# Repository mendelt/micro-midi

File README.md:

# micro-midi

This is a KiCad pcb design for a Midi input and output breakout board for microcontroller projects.

## Datasheets
- [6n137](https://www.vishay.com/docs/84732/6n137.pdf)

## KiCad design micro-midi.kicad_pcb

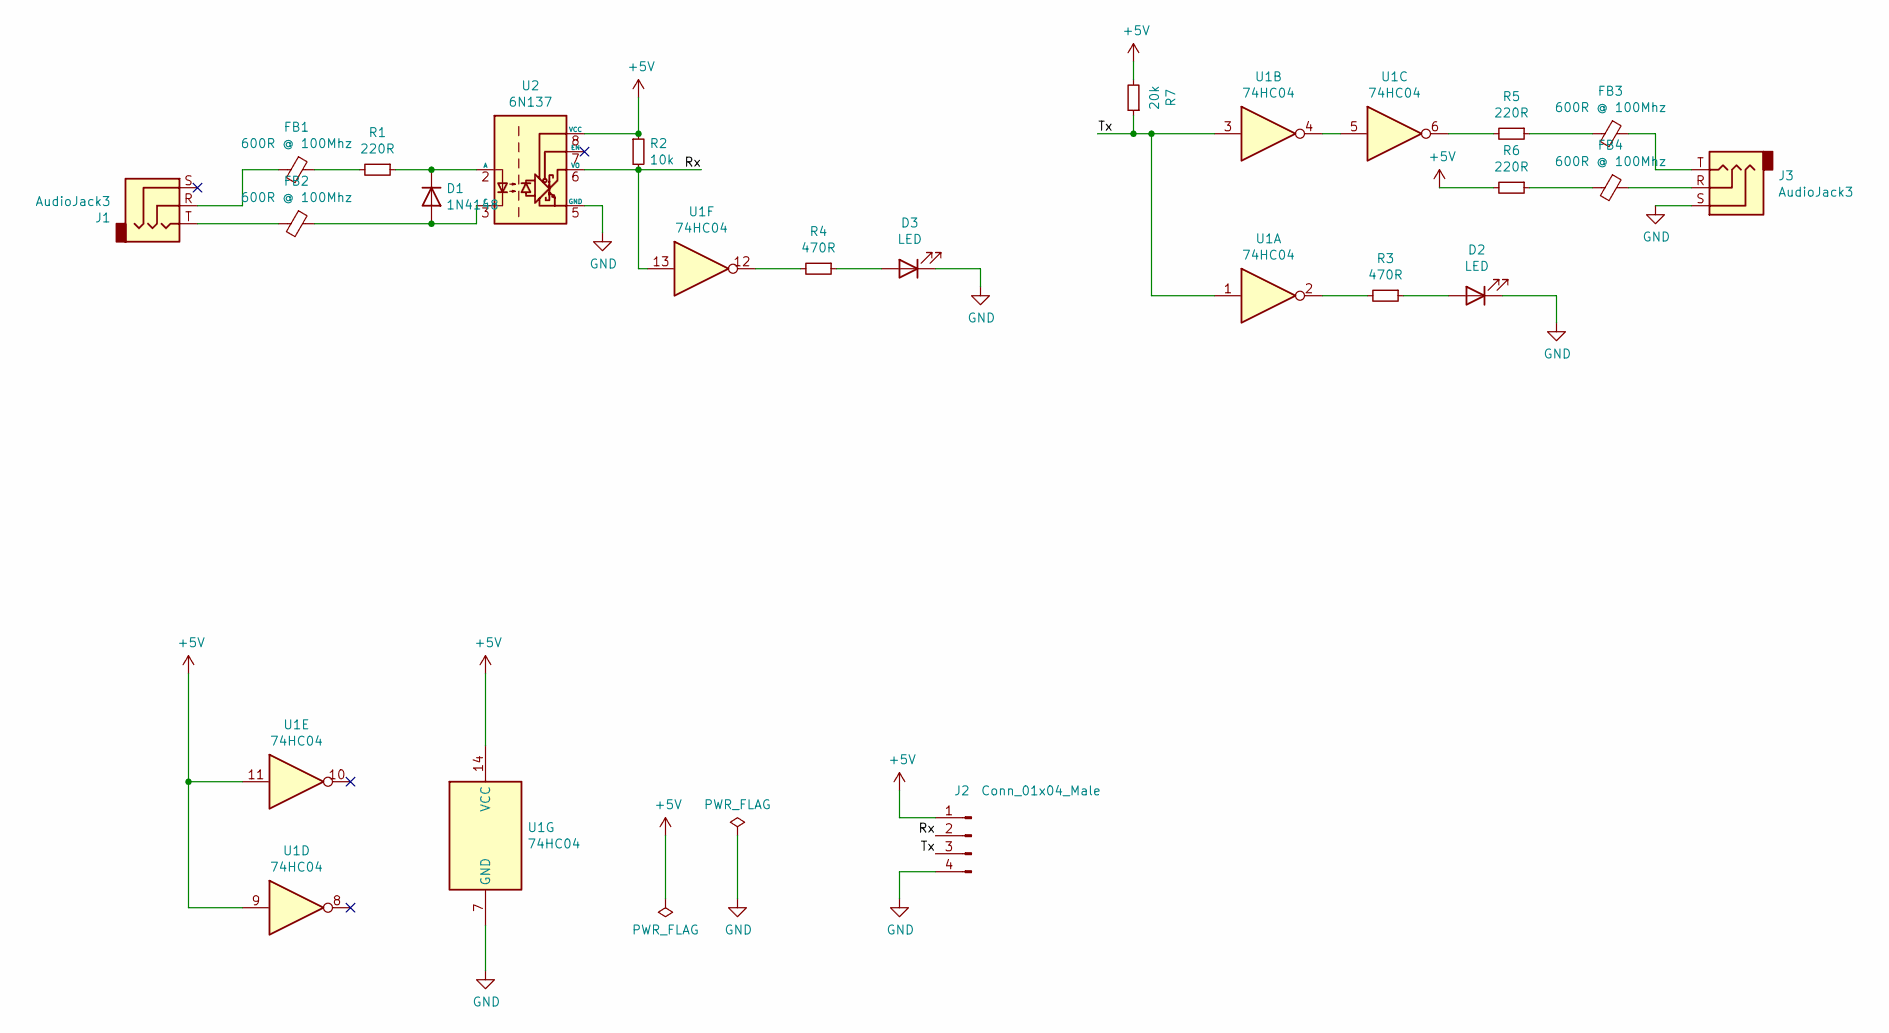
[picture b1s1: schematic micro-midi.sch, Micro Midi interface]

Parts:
D1: 1N4148; D_0805_2012Metric_Pad1.15x1.40mm_HandSolder
D2, D3: LED; LED_0805_2012Metric_Pad1.15x1.40mm_HandSolder
FB1, FB2, FB3, FB4: 600R @ 100Mhz; R_0805_2012Metric_Pad1.15x1.40mm_HandSolder; Mouser 81-BLM21A601F
J1, J3: AudioJack3; Jack_3.5mm_QingPu_WQP-PJ398SM_Vertical_CircularHoles
J2: Conn_01x04_Male; PinHeader_1x04_P2.54mm_Vertical
R1, R5, R6: 220R; R_0805_2012Metric_Pad1.15x1.40mm_HandSolder; Mouser 667-ERJ-6ENF2200V
R2: 10k; R_0805_2012Metric_Pad1.15x1.40mm_HandSolder; Mouser 667-ERJ-6ENF1002V
R3, R4: 470R; R_0805_2012Metric_Pad1.15x1.40mm_HandSolder; Mouser 667-ERJ-6ENF4700V
R7: 20k; R_0805_2012Metric_Pad1.15x1.40mm_HandSolder; Mouser 667-ERJ-6ENF2002V
U1: 74HC04; SOIC-14_3.9x8.7mm_P1.27mm
U2: 6N137; PowerIntegrations_SMD-8

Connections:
+5V: J2.1, R2.1, R6.2, R7.2, U1.9, U1.11, U1.14 (VCC), U2.8 (VCC)
/Rx: J2.2, R2.2, U1.13, U2.6 (VO)
/Tx: J2.3, R7.1, U1.1, U1.3
GND: D2.1 (K), D3.1 (K), J2.4, J3.S, U1.7 (GND), U2.5 (GND)
unnamed: D1.1 (K), R1.1, U2.2 (A)
unnamed: D1.2 (A), FB2.1, U2.3 (C)
unnamed: D2.2 (A), R3.1
unnamed: D3.2 (A), R4.1
unnamed: FB1.1, R1.2
unnamed: FB1.2, J1.R
unnamed: FB2.2, J1.T
unnamed: FB3.1, J3.T
unnamed: FB3.2, R5.1
unnamed: FB4.1, J3.R
unnamed: FB4.2, R6.1
unnamed: R3.2, U1.2
unnamed: R4.2, U1.12
unnamed: R5.2, U1.6
unnamed: U1.4, U1.5

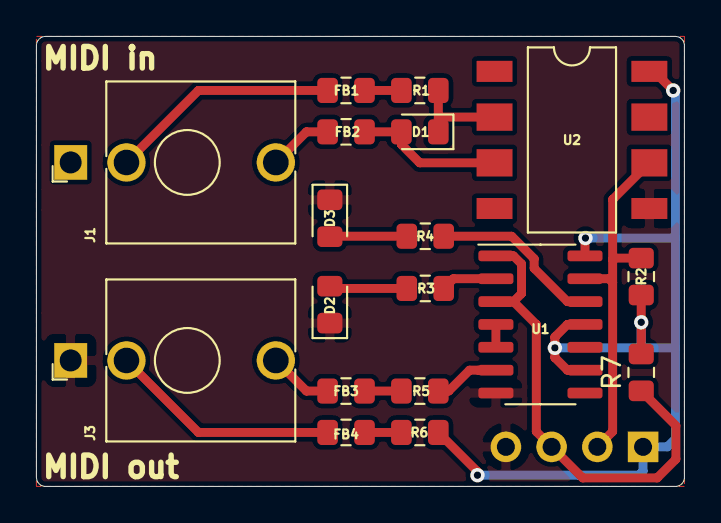
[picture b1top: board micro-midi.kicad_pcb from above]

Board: 2 copper layers, 36.0 x 25.0 mm, 19 parts (1 on the bottom side), 19 nets.

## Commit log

2020-03-26 Initialize project with first schema
2020-03-27 add footprints first try and create ratsnest
2020-03-29 add midi-out and activity leds
2020-04-16 add power flags to fix errors
2020-04-16 remove midi thru
2020-04-16 fix midi out led and ground
2020-04-16 fix midi out and add termination resistors
2020-04-21 set up schematic page settings
2020-04-28 found the right footprint for the 6n137
2020-04-28 add 6n137 datasheet link to README.md
2020-04-28 update resistor footprints to 0805
2020-04-28 update all to 0805
2020-04-28 fix U1A
2020-04-28 add pinheader footprint
2020-04-28 first try placing components
2020-04-29 switch two inverters to make routing easier
2020-04-29 some routing, rename pads on jacks to fix missing connection
2020-04-29 reshuffle schematic for clarity
2020-05-01 some routing
2020-05-01 fix board edge
2020-05-01 fix copper pours
2020-05-02 shuffle inverters to make traces fit better
2020-05-02 finish pcb routing, clean up component numbers silkscreen
2020-05-02 more compact component placement
2020-05-06 fix README.md typo
2020-05-23 redo layout for smaller board
2020-05-23 fix accidentally flipped parts
2020-06-03 move r2 to make some room
2020-06-03 reorder parts to make board more compact
2020-06-03 clean up copper
2020-06-03 change back copper fill to gnd and re-route board
2020-06-04 add back silkscreen
2020-06-04 revision 0.3.0
2020-06-04 put revision on silkscreen
2020-06-04 add ferrites to schematic
2020-06-04 add some mouser part numbers
2020-06-05 add ferrites to board
2020-06-05 rough placement for ferrites
2020-06-05 un-cross some tracks
2020-06-05 fix board size
2020-06-05 .gitignore gerbers
2020-06-06 increase board size some more
2020-06-06 precise placement
2020-06-06 re-route new layout
2020-06-06 fix back silkscreen
2020-06-07 fix misconnected input
2020-06-07 split schematics for input and output
2020-06-07 re-route
2020-06-07 add dimensions on pcb design
2020-06-08 add 20k pullup resistor to tx input.
    this allows the rx led to turn off when rx is not connected
2020-06-08 add tx pullup to the board
2020-06-08 fix rx and tx naming
